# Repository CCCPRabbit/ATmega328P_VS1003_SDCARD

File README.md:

# ATmega328P SD Card Audio Player

A standalone audio playback device built around the **ATmega328P** microcontroller. The device reads audio files stored on an **SD card** and plays them back through the **VS1003** audio decoder.

## Overview

- **MCU:** ATmega328P
- **Storage:** SD Card (FAT filesystem)
- **Audio Decoder:** VS1003
- **File System:** [FatFs](http://elm-chan.org/fsw/ff/00index_e.html) by ChaN

## How It Works

1. The ATmega328P communicates with an SD card to read audio files.
2. FatFs handles the FAT filesystem parsing, allowing files to be listed and read from the SD card.
3. The audio data is streamed to the VS1003 decoder chip, which decodes and outputs the audio.

## Third-Party Libraries

This project uses [**FatFs**](http://elm-chan.org/fsw/ff/00index_e.html), a generic FAT filesystem module created by ChaN, to handle file access on the SD card. FatFs is used under its own license terms; please refer to the FatFs documentation for details.

## License

Except for the FatFs component (which retains its original license from ChaN), all other code and content in this project are licensed under:

**Creative Commons Attribution-NonCommercial-ShareAlike 4.0 International (CC BY-NC-SA 4.0)**

You are free to share and adapt this work for non-commercial purposes, as long as you give appropriate credit and distribute your contributions under the same license. See [https://creativecommons.org/licenses/by-nc-sa/4.0/](https://creativecommons.org/licenses/by-nc-sa/4.0/) for full license details.

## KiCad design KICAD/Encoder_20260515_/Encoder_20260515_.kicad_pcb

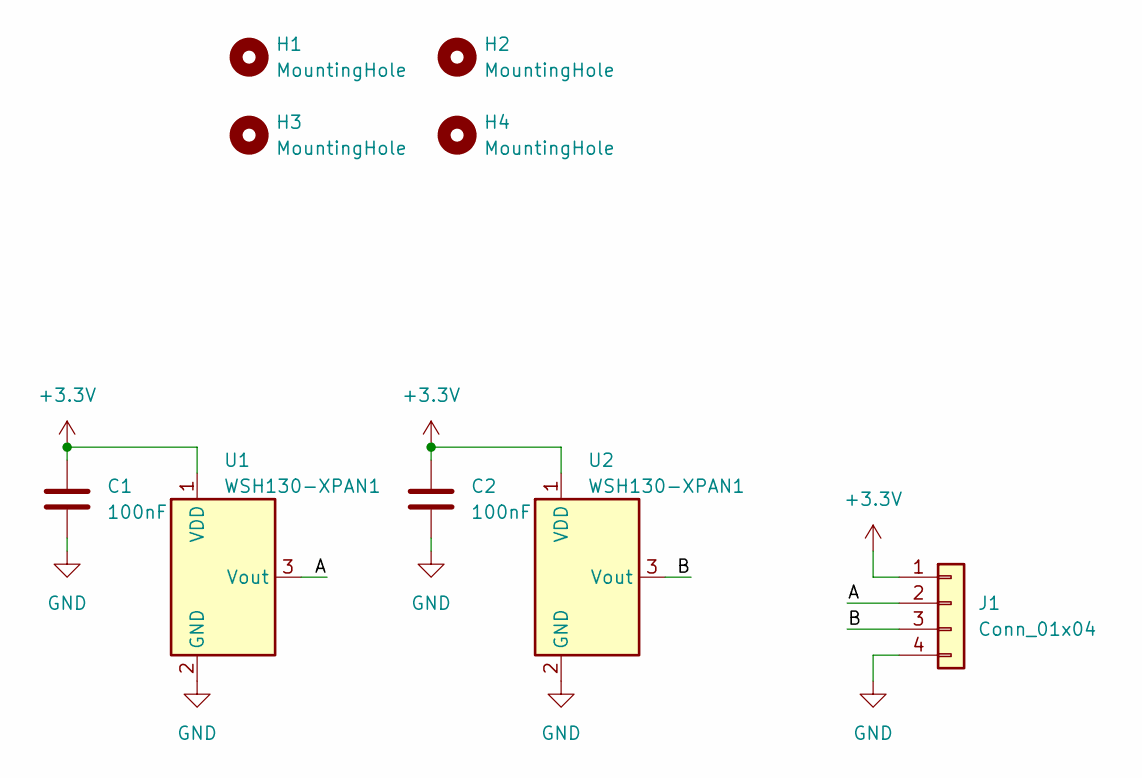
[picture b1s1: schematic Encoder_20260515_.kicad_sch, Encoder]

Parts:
C1, C2: 100nF; C_0603_1608Metric
H1, H2, H3, H4: MountingHole; MountingHole_2.2mm_M2
J1: Conn_01x04; Molex_PicoBlade_53047-0410_1x04_P1.25mm_Vertical
U1, U2: WSH130-XPAN1; TO-92S

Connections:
+3.3V: C1.1, C2.1, J1.1, U1.1 (VDD), U2.1 (VDD)
/A: J1.2, U1.3 (Vout)
/B: J1.3, U2.3 (Vout)
GND: C1.2, C2.2, J1.4, U1.2 (GND), U2.2 (GND)

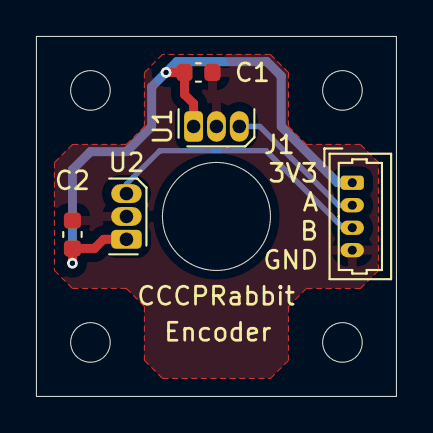
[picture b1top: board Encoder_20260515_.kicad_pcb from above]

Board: 2 copper layers, 20.0 x 20.0 mm, 9 parts (0 on the bottom side), 4 nets.

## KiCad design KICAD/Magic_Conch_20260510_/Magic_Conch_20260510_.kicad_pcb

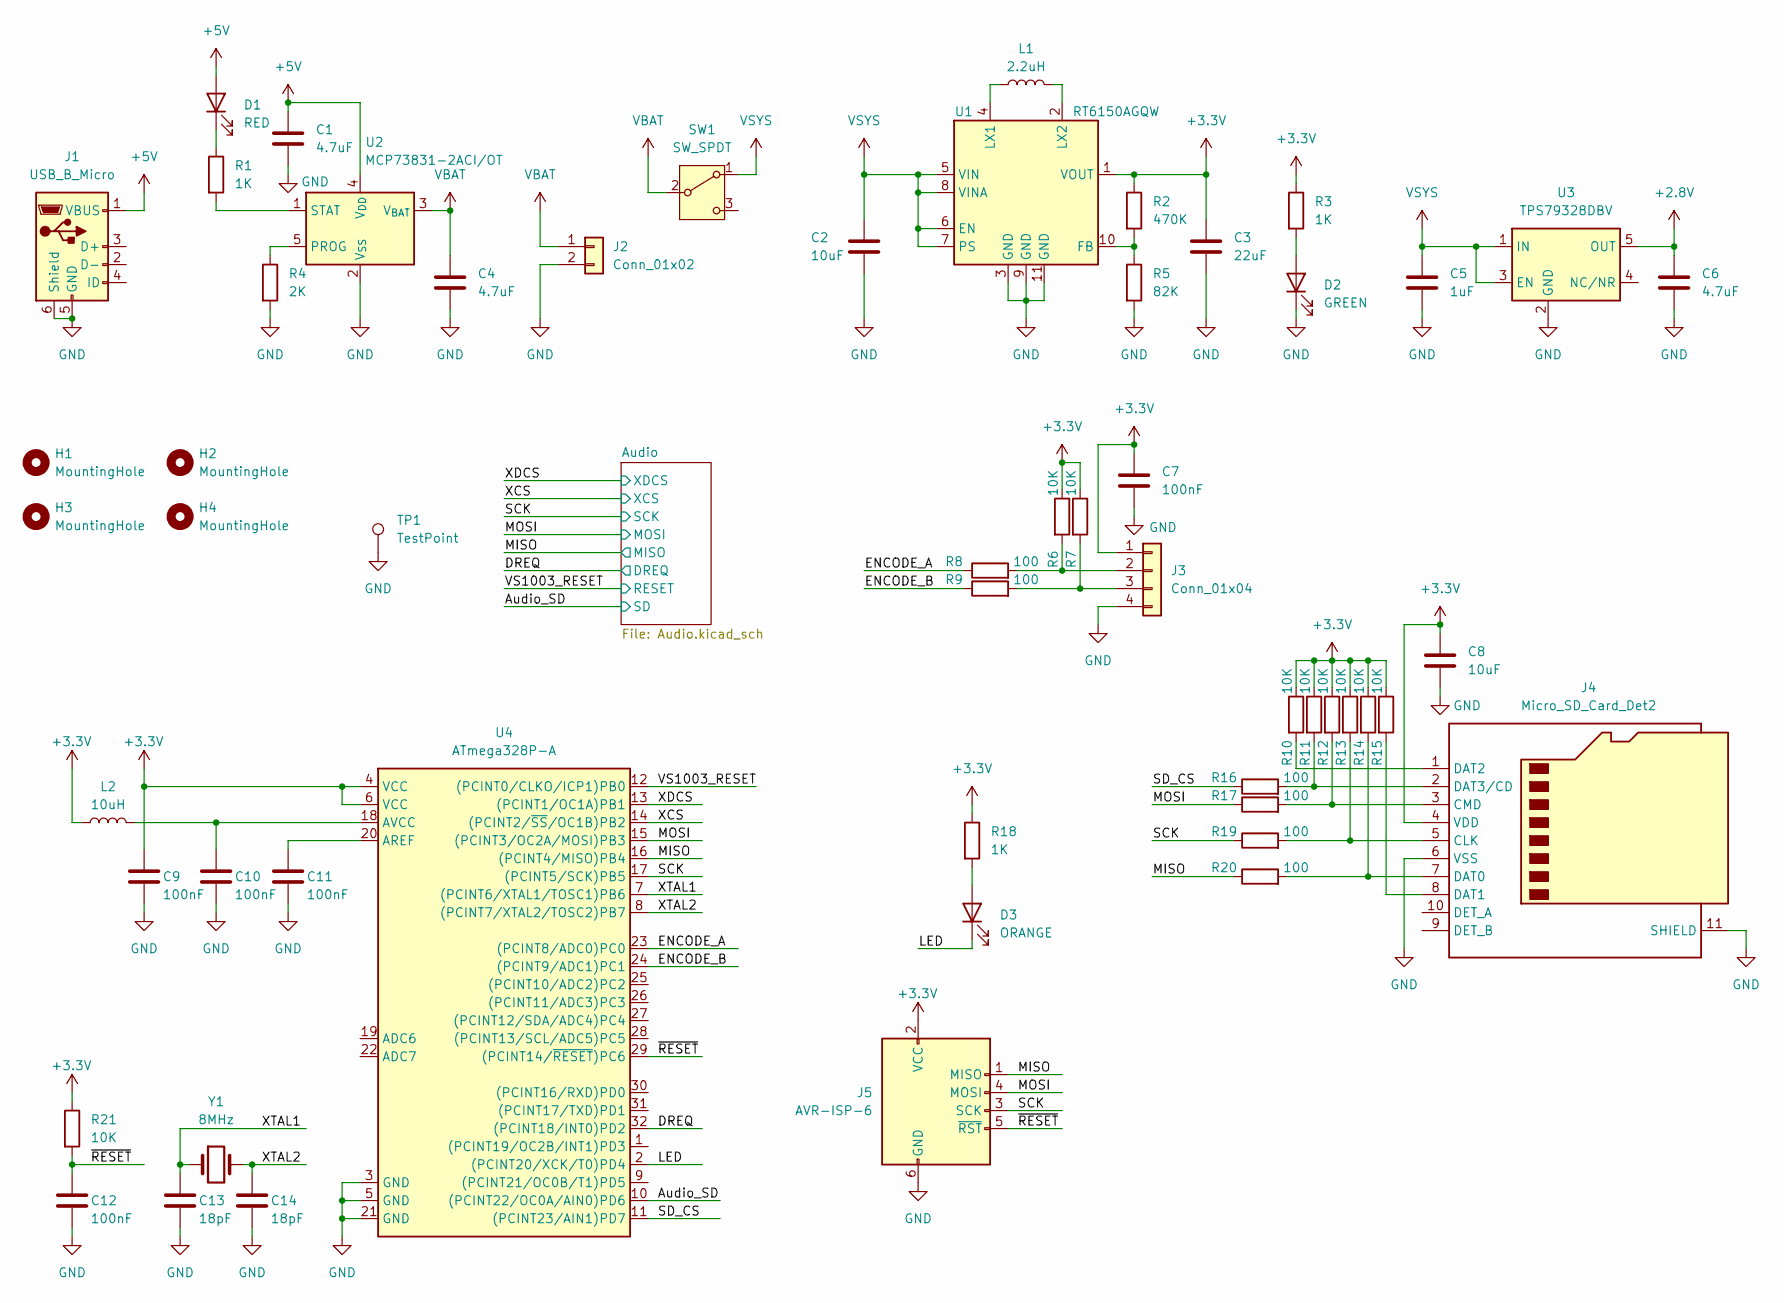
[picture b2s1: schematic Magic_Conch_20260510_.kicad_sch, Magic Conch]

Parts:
C1, C4, C6: 4.7uF; C_0603_1608Metric
C2, C8: 10uF; C_0603_1608Metric
C3: 22uF; C_0603_1608Metric
C5: 1uF; C_0603_1608Metric
C7, C9, C10, C11, C12: 100nF; C_0603_1608Metric
C13, C14: 18pF; C_0603_1608Metric
D1: RED; LED_0603_1608Metric
D2: GREEN; LED_0603_1608Metric
D3: ORANGE; LED_0603_1608Metric
H1, H2, H3, H4: MountingHole; MountingHole_3.2mm_M3
J1: USB_B_Micro; USB_Micro-B_Amphenol_10118194_Horizontal
J2: Conn_01x02; Molex_PicoBlade_53047-0210_1x02_P1.25mm_Vertical
J3: Conn_01x04; Molex_PicoBlade_53047-0410_1x04_P1.25mm_Vertical
J4: Micro_SD_Card_Det2; microSD_HC_Hirose_DM3AT-SF-PEJM5
J5: AVR-ISP-6; IDC-Header_2x03_P2.54mm_Vertical
L1: 2.2uH; L_1008_2520Metric
L2: 10uH; L_0603_1608Metric
R1, R3, R18: 1K; R_0603_1608Metric
R2: 470K; R_0603_1608Metric
R4: 2K; R_0603_1608Metric
R5: 82K; R_0603_1608Metric
R6, R7, R10, R11, R12, R13, R14, R15, R21: 10K; R_0603_1608Metric
R8, R9, R16, R17, R19, R20: 100; R_0603_1608Metric
SW1: SW_SPDT; MSL-1C2P(MID)-4mm
TP1: TestPoint; PinHeader_1x01_P2.54mm_Vertical
U1: RT6150AGQW; WDFN-10-1EP_3x3mm_P0.5mm_EP1.8x2.5mm
U2: MCP73831-2ACI/OT; SOT-23-5
U3: TPS79328DBV; SOT-23-5
U4: ATmega328P-A; TQFP-32_7x7mm_P0.8mm
Y1: 8MHz; Crystal_SMD_HC49-SD

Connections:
+2.8V: C6.1, U3.5 (OUT); also elsewhere on the board
+3.3V: C3.1, C7.1, C8.1, C9.1, J3.1, J4.4 (VDD), J5.2 (VCC), L2.1, R2.1, R3.1, R6.1, R7.1, R10.1, R11.1, R12.1, R13.1, R14.1, R15.1, R18.1, R21.1, U1.1 (VOUT), U4.4 (VCC), U4.6 (VCC); also elsewhere on the board
+5V: C1.1, D1.2 (A), J1.1 (VBUS), U2.4 (V_{DD})
/Audio_SD: U4.10 ((PCINT22/OC0A/AIN0)PD6); also elsewhere on the board
/DREQ: U4.32 ((PCINT18/INT0)PD2); also elsewhere on the board
/ENCODE_A: R8.1, U4.23 ((PCINT8/ADC0)PC0)
/ENCODE_B: R9.1, U4.24 ((PCINT9/ADC1)PC1)
/LED: D3.1 (K), U4.2 ((PCINT20/XCK/T0)PD4)
/MISO: J5.1 (MISO), R20.1, U4.16 ((PCINT4/MISO)PB4); also elsewhere on the board
/MOSI: J5.4 (MOSI), R17.1, U4.15 ((PCINT3/OC2A/MOSI)PB3); also elsewhere on the board
/SCK: J5.3 (SCK), R19.1, U4.17 ((PCINT5/SCK)PB5); also elsewhere on the board
/SD_CS: R16.1, U4.11 ((PCINT23/AIN1)PD7)
/VS1003_RESET: U4.12 ((PCINT0/CLKO/ICP1)PB0); also elsewhere on the board
/XCS: U4.14 ((PCINT2/~SS/OC1B)PB2); also elsewhere on the board
/XDCS: U4.13 ((PCINT1/OC1A)PB1); also elsewhere on the board
/XTAL1: C13.1, U4.7 ((PCINT6/XTAL1/TOSC1)PB6), Y1.1
/XTAL2: C14.1, U4.8 ((PCINT7/XTAL2/TOSC2)PB7), Y1.2
/~RESET: C12.1, J5.5 (~RST), R21.2, U4.29 ((PCINT14/~RESET)PC6)
GND: C1.2, C2.2, C3.2, C4.2, C5.2, C6.2, C7.2, C8.2, C9.2, C10.2, C11.2, C12.2, C13.2, C14.2, D2.1 (K), J1.5 (GND), J1.6 (Shield), J2.2, J3.4, J4.6 (VSS), J4.11 (SHIELD), J5.6 (GND), R4.2, R5.2, TP1.1, U1.3 (GND), U1.9 (GND), U1.11 (GND), U2.2 (V_{SS}), U3.2 (GND), U4.3 (GND), U4.5 (GND), U4.21 (GND); also elsewhere on the board
unnamed: D1.1 (K), R1.1
unnamed: D2.2 (A), R3.2
unnamed: D3.2 (A), R18.2
unnamed: J3.2, R6.2, R8.2
unnamed: J3.3, R7.2, R9.2
unnamed: J4.5 (CLK), R13.2, R19.2
unnamed: J4.3 (CMD), R12.2, R17.2
unnamed: J4.7 (DAT0), R14.2, R20.2
unnamed: J4.8 (DAT1), R15.2
unnamed: J4.1 (DAT2), R10.2
unnamed: J4.2 (DAT3/CD), R11.2, R16.2
unnamed: R2.2, R5.1, U1.10 (FB)
unnamed: L1.1, U1.4 (LX1)
unnamed: L1.2, U1.2 (LX2)
unnamed: R4.1, U2.5 (PROG)
unnamed: R1.2, U2.1 (STAT)
unnamed: C11.1, U4.20 (AREF)
unnamed: C10.1, L2.2, U4.18 (AVCC)
VBAT: C4.1, J2.1, SW1.2 (B), U2.3 (V_{BAT})
VSYS: C2.1, C5.1, SW1.1 (A), U1.5 (VIN), U1.6 (EN), U1.7 (PS), U1.8 (VINA), U3.1 (IN), U3.3 (EN)

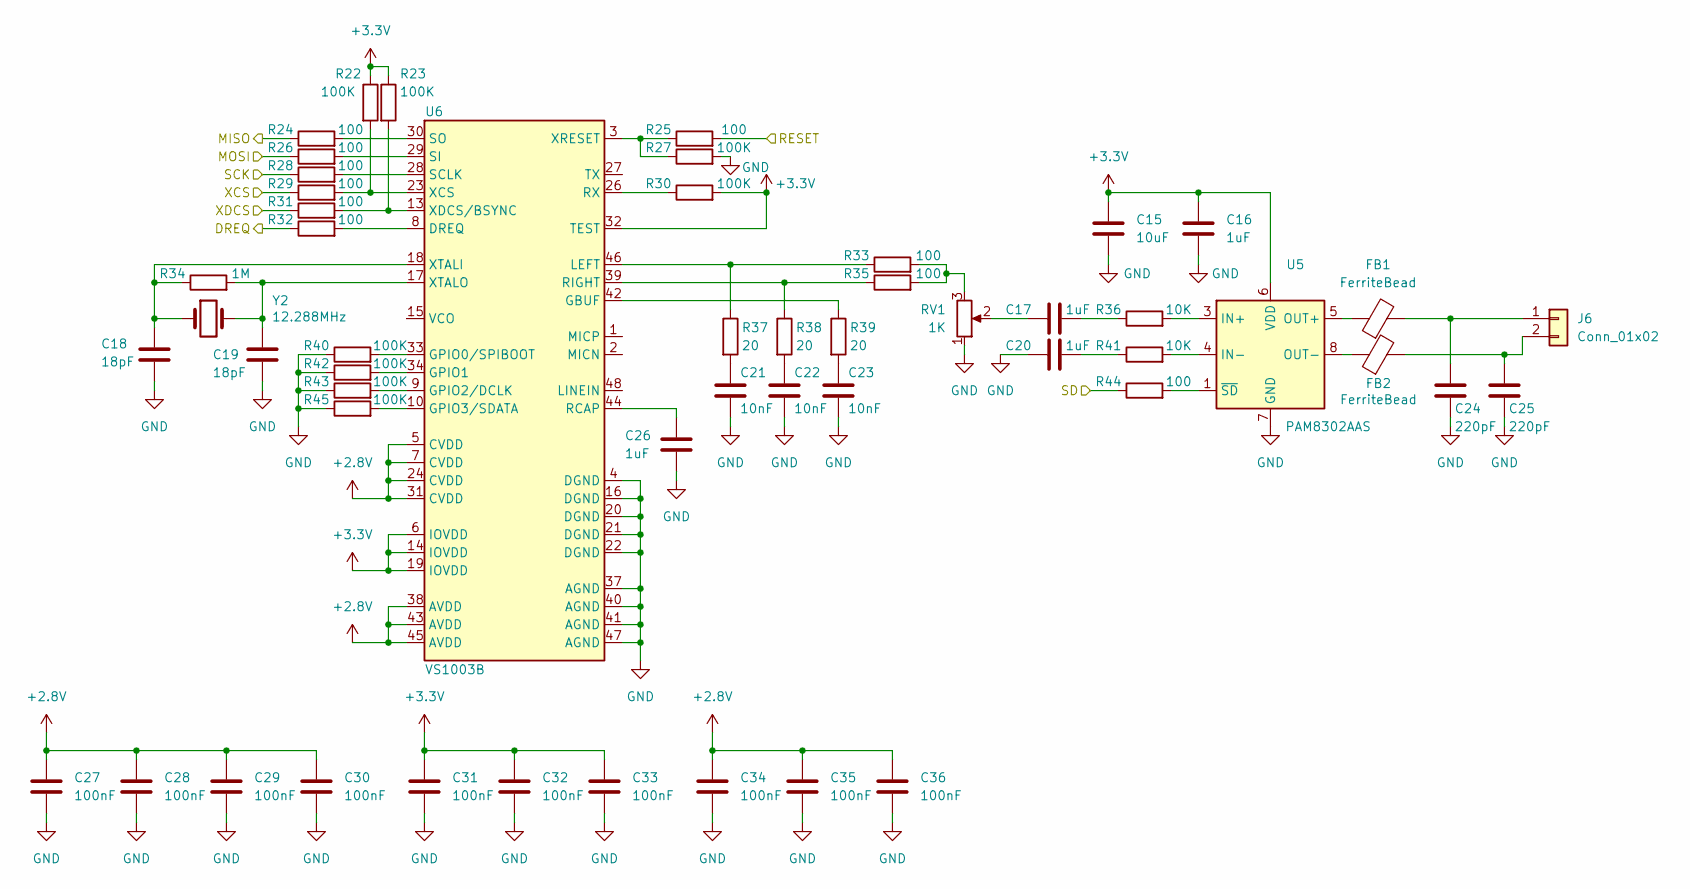
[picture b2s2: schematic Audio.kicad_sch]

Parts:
C15: 10uF; C_0603_1608Metric
C16, C17, C20, C26: 1uF; C_0603_1608Metric
C18, C19: 18pF; C_0603_1608Metric
C21, C22, C23: 10nF; C_0603_1608Metric
C24, C25: 220pF; C_0603_1608Metric
C27, C28, C29, C30, C31, C32, C33, C34, C35, C36: 100nF; C_0603_1608Metric
FB1, FB2: FerriteBead; L_0603_1608Metric
J6: Conn_01x02; Molex_PicoBlade_53047-0210_1x02_P1.25mm_Vertical
R22, R23, R27, R30, R40, R42, R43, R45: 100K; R_0603_1608Metric
R24, R25, R26, R28, R29, R31, R32, R33, R35, R44: 100; R_0603_1608Metric
R34: 1M; R_0603_1608Metric
R36, R41: 10K; R_0603_1608Metric
R37, R38, R39: 20; R_0603_1608Metric
RV1: 1K; Potentiometer_Bourns_3362P_Vertical
U5: PAM8302AAS; MSOP-8_3x3mm_P0.65mm
U6: VS1003B; LQFP-48_7x7mm_P0.5mm
Y2: 12.288MHz; Crystal_SMD_HC49-SD

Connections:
+2.8V: C27.1, C28.1, C29.1, C30.1, C34.1, C35.1, C36.2, U6.5 (CVDD), U6.7 (CVDD), U6.24 (CVDD), U6.31 (CVDD), U6.38 (AVDD), U6.43 (AVDD), U6.45 (AVDD); also elsewhere on the board
+3.3V: C15.1, C16.1, C31.1, C32.1, C33.1, R22.1, R23.1, R30.2, U5.6 (VDD), U6.6 (IOVDD), U6.14 (IOVDD), U6.19 (IOVDD), U6.32 (TEST); also elsewhere on the board
/Audio_SD: R44.1; also elsewhere on the board
/DREQ: R32.1; also elsewhere on the board
/MISO: R24.1; also elsewhere on the board
/MOSI: R26.1; also elsewhere on the board
/SCK: R28.1; also elsewhere on the board
/VS1003_RESET: R25.2; also elsewhere on the board
/XCS: R29.1; also elsewhere on the board
/XDCS: R31.1; also elsewhere on the board
GND: C15.2, C16.2, C18.2, C19.2, C20.1, C21.2, C22.2, C23.2, C24.2, C25.2, C26.2, C27.2, C28.2, C29.2, C30.2, C31.2, C32.2, C33.2, C34.2, C35.2, C36.1, R27.2, R40.1, R42.1, R43.1, R45.1, RV1.1, U5.7 (GND), U6.4 (DGND), U6.16 (DGND), U6.20 (DGND), U6.21 (DGND), U6.22 (DGND), U6.37 (AGND), U6.40 (AGND), U6.41 (AGND), U6.47 (AGND); also elsewhere on the board
unnamed: C17.1, RV1.2
unnamed: C17.2, R36.1
unnamed: C20.2, R41.1
unnamed: C21.1, R37.2
unnamed: C22.1, R38.2
unnamed: C23.1, R39.2
unnamed: C24.1, FB1.2, J6.1
unnamed: C25.1, FB2.2, J6.2
unnamed: R33.2, R35.2, RV1.3
unnamed: R36.2, U5.3 (IN+)
unnamed: R41.2, U5.4 (IN-)
unnamed: FB1.1, U5.5 (OUT+)
unnamed: FB2.1, U5.8 (OUT-)
unnamed: R44.2, U5.1 (~SD)
unnamed: R32.2, U6.8 (DREQ)
unnamed: R39.1, U6.42 (GBUF)
unnamed: R40.2, U6.33 (GPIO0/SPIBOOT)
unnamed: R42.2, U6.34 (GPIO1)
unnamed: R43.2, U6.9 (GPIO2/DCLK)
unnamed: R45.2, U6.10 (GPIO3/SDATA)
unnamed: R33.1, R37.1, U6.46 (LEFT)
unnamed: C26.1, U6.44 (RCAP)
unnamed: R35.1, R38.1, U6.39 (RIGHT)
unnamed: R30.1, U6.26 (RX)
unnamed: R28.2, U6.28 (SCLK)
unnamed: R26.2, U6.29 (SI)
unnamed: R24.2, U6.30 (SO)
unnamed: R22.2, R29.2, U6.23 (XCS)
unnamed: R23.2, R31.2, U6.13 (XDCS/BSYNC)
unnamed: R25.1, R27.1, U6.3 (XRESET)
unnamed: C18.1, R34.1, U6.18 (XTALI), Y2.1
unnamed: C19.1, R34.2, U6.17 (XTALO), Y2.2

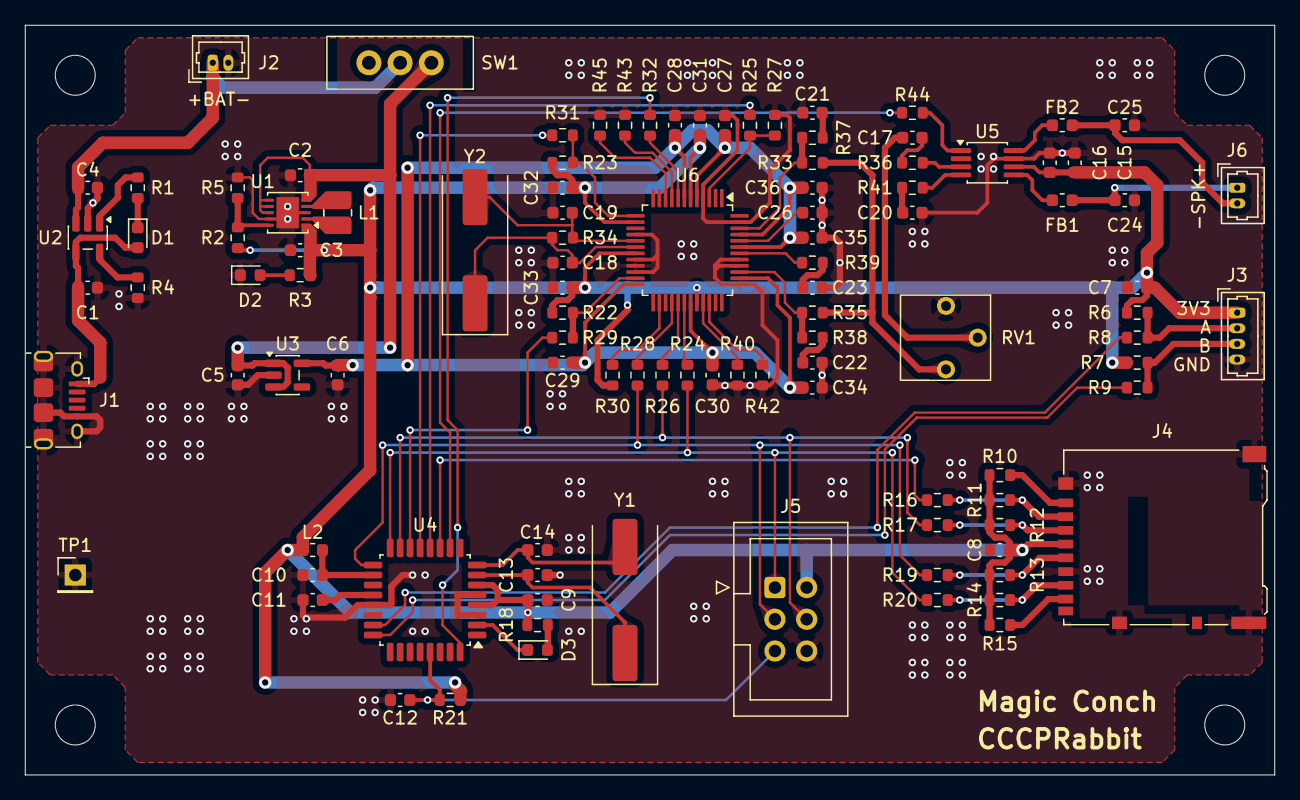
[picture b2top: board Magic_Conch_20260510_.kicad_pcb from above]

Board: 2 copper layers, 100.0 x 60.0 mm, 109 parts (0 on the bottom side), 71 nets.

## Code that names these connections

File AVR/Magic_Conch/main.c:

/**
 * @file main.c
 * @author CCCPRabbit
 * @date 2026-06-25
 * @brief Main function
 */

#include <avr/io.h>
#include <avr/interrupt.h>
#include <util/delay.h>
#include <stdio.h>
#include <string.h>
#include <stdlib.h>
#include "main.h"
#include "spi.h"
#include "usart_interrupt.h"
#include "vs1003.h"
#include "ff.h"
#include "mmc_avr.h"

#define LED_PORT    PORTD
#define LED_PIN     PD4
#define LED_ON      LED_PORT&=~(1<<LED_PIN)
#define LED_OFF     LED_PORT|=1<<LED_PIN
#define LED_TOGGLE  LED_PORT^=1<<LED_PIN
#define AUDIO_SHUTDOWN_PORT PORTD
#define AUDIO_SHUTDOWN_PIN  PD6
#define ENCODER_PIN     PINC
#define ENCODER_A_PIN   PC0
#define ENCODER_B_PIN   PC1

#define STOP_STATE  0
#define WAIT_STATE  1
#define PLAY_STATE  2

#define FILE_COUNT_MAX  50

// Voltage Reference: AVCC pin
#define ADC_VREF_TYPE ((0<<REFS1) | (1<<REFS0) | (0<<ADLAR))

volatile uint16_t tick=0;

#ifdef DEBUG
char usart_string[32];
#endif

uint8_t SpinCheck(uint16_t encoder_count);
uint16_t Encoder(void);
uint8_t CountFiles(char file_path_list[][FF_SFN_BUF+1]);
unsigned int ReadADC(unsigned char adc_input);

ISR(TIMER0_COMPA_vect)
{
    static uint8_t _10ms_counter=0;
    tick++;

    _10ms_counter++;
    if(_10ms_counter>=10)
    {
        _10ms_counter=0;
        mmc_disk_timerproc();
    }
}

int main(){
    // Add your code here and press Ctrl + Shift + B to build
    FATFS fs;
    FIL fil;
    FRESULT res;
    volatile uint16_t led_tick=0;
    uint8_t state=WAIT_STATE,file_count,mp3_buffer[32];
    char file_path_list[FILE_COUNT_MAX][FF_SFN_BUF+1];
    uint16_t adc_value;

    SD_CS_PORT|=(1<<SD_CS_PIN);
    DDRD=(1<<SD_CS_PIN)|(1<<AUDIO_SHUTDOWN_PIN)|(1<<LED_PIN);

    AUDIO_SHUTDOWN_PORT|=(1<<AUDIO_SHUTDOWN_PIN);

    //timer0 Clock : 125.000 kHz, Mode: CTC top=OCR0A, Timer Period: 1 ms
    TCCR0A=(0<<COM0A1) | (0<<COM0A0) | (0<<COM0B1) | (0<<COM0B0) | (1<<WGM01) | (0<<WGM00);
    TCCR0B=(0<<WGM02) | (0<<CS02) | (1<<CS01) | (1<<CS00);
    TCNT0=0x00;
    OCR0A=0x7C;
    OCR0B=0x00;

    TIMSK0=(0<<OCIE0B) | (1<<OCIE0A) | (0<<TOIE0);//timer interrupt enable

    // ADC Clock frequency: 1000.000 kHz
    // ADC Voltage Reference: AVCC pin
    DIDR0=(0<<ADC5D) | (0<<ADC4D) | (0<<ADC3D) | (0<<ADC2D) | (0<<ADC1D) | (0<<ADC0D);
    ADMUX=ADC_VREF_TYPE;
    ADCSRA=(1<<ADEN) | (0<<ADSC) | (0<<ADATE) | (0<<ADIF) | (0<<ADIE) | (1<<ADPS2) | (1<<ADPS1) | (1<<ADPS0);
    ADCSRB=(0<<ADTS2) | (0<<ADTS1) | (0<<ADTS0);

    #ifdef DEBUG
    InitUART(8,1);
    #endif
    sei();
    SPIInit();
    VS1003_Init();

    res=f_mount(&fs,"",0);
    #ifdef DEBUG
    sprintf(usart_string,"f_mount %d\r",res);
    USARTPuts(usart_string);
    #endif
    file_count=CountFiles(file_path_list);
    #ifdef DEBUG
    sprintf(usart_string,"file_count %d\r",file_count);
    USARTPuts(usart_string);
    for(uint8_t i=0;i<file_count;i++){
        sprintf(usart_string,"%s\r",file_path_list[i]);
        USARTPuts(usart_string);
    }
    #endif
    if(file_count==0){
        #ifdef DEBUG
        sprintf(usart_string,"no file\r");
        USARTPuts(usart_string);
        #endif
        while(1){}
    }

    for(uint8_t i=0;i<6;i++)
    adc_value^=ReadADC(2+i);
    srand(adc_value);//TODO adc as seed
    #ifdef DEBUG
    sprintf(usart_string,"seed %d\r",adc_value);
    USARTPuts(usart_string);
    #endif

    while(1){
        uint8_t spin;
        uint16_t encoder_count;
        encoder_count=Encoder();
        spin=SpinCheck(encoder_count);

        switch(state){
        case STOP_STATE:
            if(spin){
                uint8_t random_num;
                state=PLAY_STATE;
                random_num=rand()%file_count;
                #ifdef DEBUG
                sprintf(usart_string,"rand %d\r",random_num);
                USARTPuts(usart_string);
                #endif
                res=f_open(&fil,file_path_list[random_num],FA_READ);
                #ifdef DEBUG
                sprintf(usart_string,"f_open %d\r",res);
                USARTPuts(usart_string);
                #endif
            }
            break;
        case PLAY_STATE:
            if (VS_DREQ_PIN_REG & (1 << VS_DREQ_PIN)) {
                uint16_t bytes_read=0;
                f_read(&fil, mp3_buffer, 32, &bytes_read);
                if(bytes_read>=0)
                    VS1003_SendMusicData(mp3_buffer, bytes_read);
                else
                    state=WAIT_STATE;
            }

            if(!spin){
                state=STOP_STATE;
                VS1003_WriteRegister(SCI_MODE,0x0804|SM_OUTOFWAV);
                f_close(&fil);
            }
            break;
        case WAIT_STATE:
            if(!spin){
                state=STOP_STATE;
            }
            break;
        default:state=STOP_STATE;
        }

        if(tick-led_tick>=300){
            led_tick=tick;
            LED_TOGGLE;
        }
    }

    return 0;
}

uint8_t SpinCheck(uint16_t encoder_count){
    static uint16_t old_tick=0,last_count=0;
    static uint8_t state=0;
    switch(state){
    case 0:
        if((int16_t)encoder_count-(int16_t)last_count>=3){
            old_tick=tick;
            last_count=encoder_count;
            state=1;
        }
        else if(tick-old_tick>=500){
            old_tick=tick;
            last_count=encoder_count;
        }
        break;
    case 1:
        if((int16_t)encoder_count-(int16_t)last_count>0){
            old_tick=tick;
            last_count=encoder_count;
        }
        else if(tick-old_tick>300){
            old_tick=tick;
            state=0;
        }
    }
    return state;
}

uint16_t Encoder(void){
    static uint8_t encoder_state=0;
    static uint16_t encoder_count=0;
    encoder_state=((encoder_state<<2)&0x0c)|(ENCODER_PIN&((1<<ENCODER_A_PIN)|(1<<ENCODER_B_PIN)));
    switch(encoder_state){
    case 0x0d:
    case 0x0b:
    case 0x02:
    case 0x04:encoder_count++;break;
    case 0x07:
    case 0x0e:
    case 0x08:
    case 0x01:encoder_count--;break;
    }
    return encoder_count;
}

uint8_t CountFiles(char file_path_list[][FF_SFN_BUF+1]){
    DIR dir;
    FILINFO fno;
    FRESULT res;
    int count = 0;

    res = f_opendir(&dir, "");
    #ifdef DEBUG
    sprintf(usart_string,"f_opendir %d\r",res);
    USARTPuts(usart_string);
    #endif
    for (;;)
    {
        res = f_readdir(&dir, &fno);
        if (res != FR_OK || fno.fname[0] == 0) break;
        memcpy(file_path_list[count],fno.fname,FF_SFN_BUF+1);
        #ifdef DEBUG
        sprintf(usart_string,"f_readdir %d\r",res);
        USARTPuts(usart_string);
        #endif

        // 디렉토리, 볼륨레이블, 숨김/시스템 파일 제외
        if (fno.fattrib & (AM_DIR | AM_HID | AM_SYS))
        {
            continue;
        }

        count++;
    }
    res=f_closedir(&dir);
    #ifdef DEBUG
    sprintf(usart_string,"f_closedir %d\r",res);
    USARTPuts(usart_string);
    #endif

    return count;
}

unsigned int ReadADC(unsigned char adc_input)
{
    ADMUX=adc_input | ADC_VREF_TYPE;
    _delay_us(10);
    ADCSRA|=(1<<ADSC);
    while ((ADCSRA & (1<<ADIF))==0);
    ADCSRA|=(1<<ADIF);
    return ADCW;
}
